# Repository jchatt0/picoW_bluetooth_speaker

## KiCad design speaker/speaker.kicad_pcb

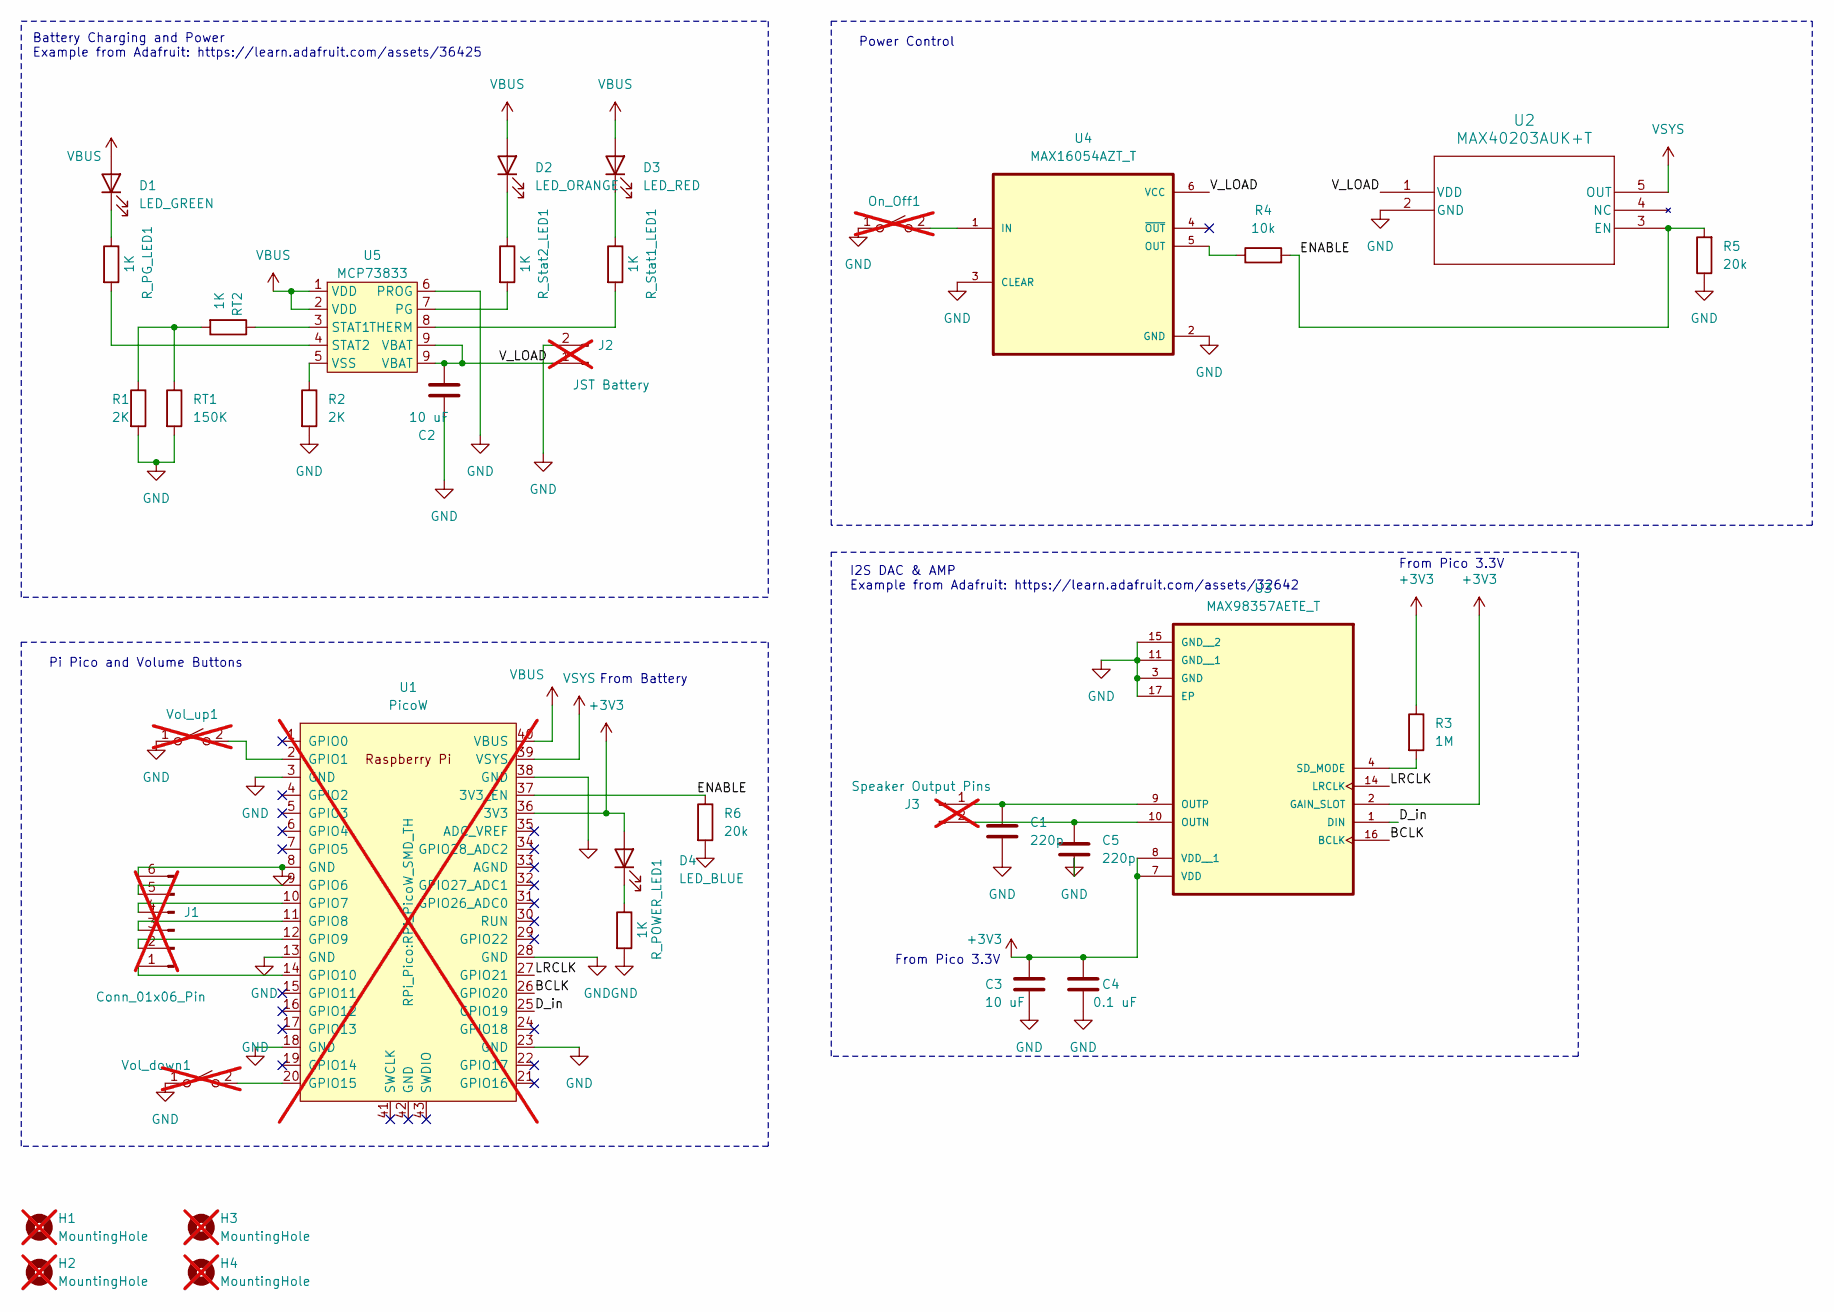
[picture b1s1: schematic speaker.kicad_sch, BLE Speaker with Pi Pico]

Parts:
C1, C5: 220p; C_0402_1005Metric_Pad0.74x0.62mm_HandSolder; MPN 0603B221K500CT
C2, C3: 10 uF; C_0603_1608Metric; MPN CL10A106MQ8NNNC
C4: 0.1 uF; C_0603_1608Metric; MPN CC0603KRX7R7BB104
D1: LED_GREEN; LED_0402_1005Metric_Pad0.77x0.64mm_HandSolder; MPN 150040GS73240
D2: LED_ORANGE; LED_0402_1005Metric_Pad0.77x0.64mm_HandSolder; MPN SML-LX0402SOC-TR
D3: LED_RED; LED_0402_1005Metric_Pad0.77x0.64mm_HandSolder; MPN XZMDK68W-2
D4: LED_BLUE; LED_0402_1005Metric_Pad0.77x0.64mm_HandSolder; MPN XZMDK68W-2
H1, H2, H3, H4: MountingHole; MountingHole_2mm; not fitted
J1: Conn_01x06_Pin; PinHeader_1x06_P1.00mm_Horizontal; not fitted
J2: JST Battery; JST_PH_S2B-PH-SM4-TB_1x02-1MP_P2.00mm_Horizontal; not fitted
J3: Speaker Output Pins; TerminalBlock_TE_282834-2_1x02_P2.54mm_Horizontal; not fitted
On_Off1: SW_SPST; SW_PUSH_6mm_H9.5mm; not fitted
R1, R2: 2K; R_0603_1608Metric; MPN ERJ-3EKF2001V
R3: 1M; R_0603_1608Metric_Pad0.98x0.95mm_HandSolder; MPN ERJ-3EKF1004V
R4: 10k; R_0603_1608Metric_Pad0.98x0.95mm_HandSolder; MPN RC0603FR-0710KL
R5, R6: 20k; R_0603_1608Metric_Pad0.98x0.95mm_HandSolder; MPN ERJ-3EKF2002V
RT1: 150K; R_0603_1608Metric; MPN RC0603FR-07150KL
RT2: 1K; R_0603_1608Metric; MPN RC0603FR-071KL
R_PG_LED1: 1K; R_0603_1608Metric; MPN RC0603FR-071KL
R_POWER_LED1: 1K; R_0603_1608Metric; MPN RC0603FR-071KL
R_Stat1_LED1, R_Stat2_LED1: 1K; R_0603_1608Metric; MPN RC0603FR-071KL
U1: PicoW; RPi_PicoW_SMD_TH; not fitted
U2: MAX40203AUK+T; 21-0057F_MXM; MPN MAX40203AUK+T
U3: MAX98357AETE_T; QFN50P300X300X80-17N; MPN MAX98357AETE_T
U4: MAX16054AZT_T; TSOT-23-6_HandSoldering; MPN MAX16054AZT_T
U5: MCP73833; MSOP10_MC_MCH-L; MPN MCP73833-CNI/UN
Vol_down1: SW_SPST; SW_PUSH_6mm_H8mm; not fitted
Vol_up1: SW_SPST; SW_PUSH_6mm_H9.5mm; not fitted

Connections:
+3V3: C3.1, C4.1, D4.2 (A), R3.1, U1.36 (3V3), U3.2 (GAIN_SLOT), U3.7 (VDD), U3.8 (VDD__1)
/BCLK: U1.26 (GPIO20), U3.16 (BCLK)
/D_in: U1.25 (GPIO19), U3.1 (DIN)
/ENABLE: R4.2, R5.2, R6.1, U1.37 (3V3_EN), U2.3 (EN)
/LRCLK: U1.27 (GPIO21), U3.14 (LRCLK)
/V_LOAD: C2.1, J2.1, U2.1 (VDD), U4.6 (VCC), U5.9 (VBAT)
GND: C1.2, C2.2, C3.2, C4.2, C5.2, J1.6, J2.2, On_Off1.1 (A), R1.2, R2.2, R5.1, R6.2, RT1.2, R_POWER_LED1.2, U1.3 (GND), U1.8 (GND), U1.13 (GND), U1.18 (GND), U1.23 (GND), U1.28 (GND), U1.38 (GND), U2.2 (GND), U3.3 (GND), U3.11 (GND__1), U3.15 (GND__2), U3.17 (EP), U4.2 (GND), U4.3 (CLEAR), U5.6 (PROG), Vol_down1.1 (A), Vol_up1.1 (A)
unnamed: D1.1 (K), R_PG_LED1.1
unnamed: D2.1 (K), R_Stat2_LED1.1
unnamed: D3.1 (K), R_Stat1_LED1.1
unnamed: D4.1 (K), R_POWER_LED1.1
unnamed: J1.1, U1.14 (GPIO10)
unnamed: J1.2, U1.12 (GPIO9)
unnamed: J1.3, U1.11 (GPIO8)
unnamed: J1.4, U1.10 (GPIO7)
unnamed: J1.5, U1.9 (GPIO6)
unnamed: C1.1, J3.1, U3.9 (OUTP)
unnamed: C5.1, J3.2, U3.10 (OUTN)
unnamed: On_Off1.2 (B), U4.1 (IN)
unnamed: R1.1, RT1.1, RT2.2
unnamed: U1.2 (GPIO1), Vol_up1.2 (B)
unnamed: U1.20 (GPIO15), Vol_down1.2 (B)
unnamed: R3.2, U3.4 (SD_MODE)
unnamed: R4.1, U4.5 (OUT)
unnamed: R_Stat2_LED1.2, U5.7 (PG)
unnamed: RT2.1, U5.3 (STAT1)
unnamed: R_PG_LED1.2, U5.4 (STAT2)
unnamed: R_Stat1_LED1.2, U5.8 (THERM)
unnamed: R2.1, U5.5 (VSS)
VBUS: D1.2 (A), D2.2 (A), D3.2 (A), U1.40 (VBUS), U5.1 (VDD), U5.2 (VDD)
VSYS: U1.39 (VSYS), U2.5 (OUT)

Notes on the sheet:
From Battery
From Pico 3.3V
Power Control
Battery Charging and Power Example from Adafruit: https://learn.adafruit.com/assets/36425
Pi Pico and Volume Buttons
I2S DAC & AMP Example from Adafruit: https://learn.adafruit.com/assets/32642

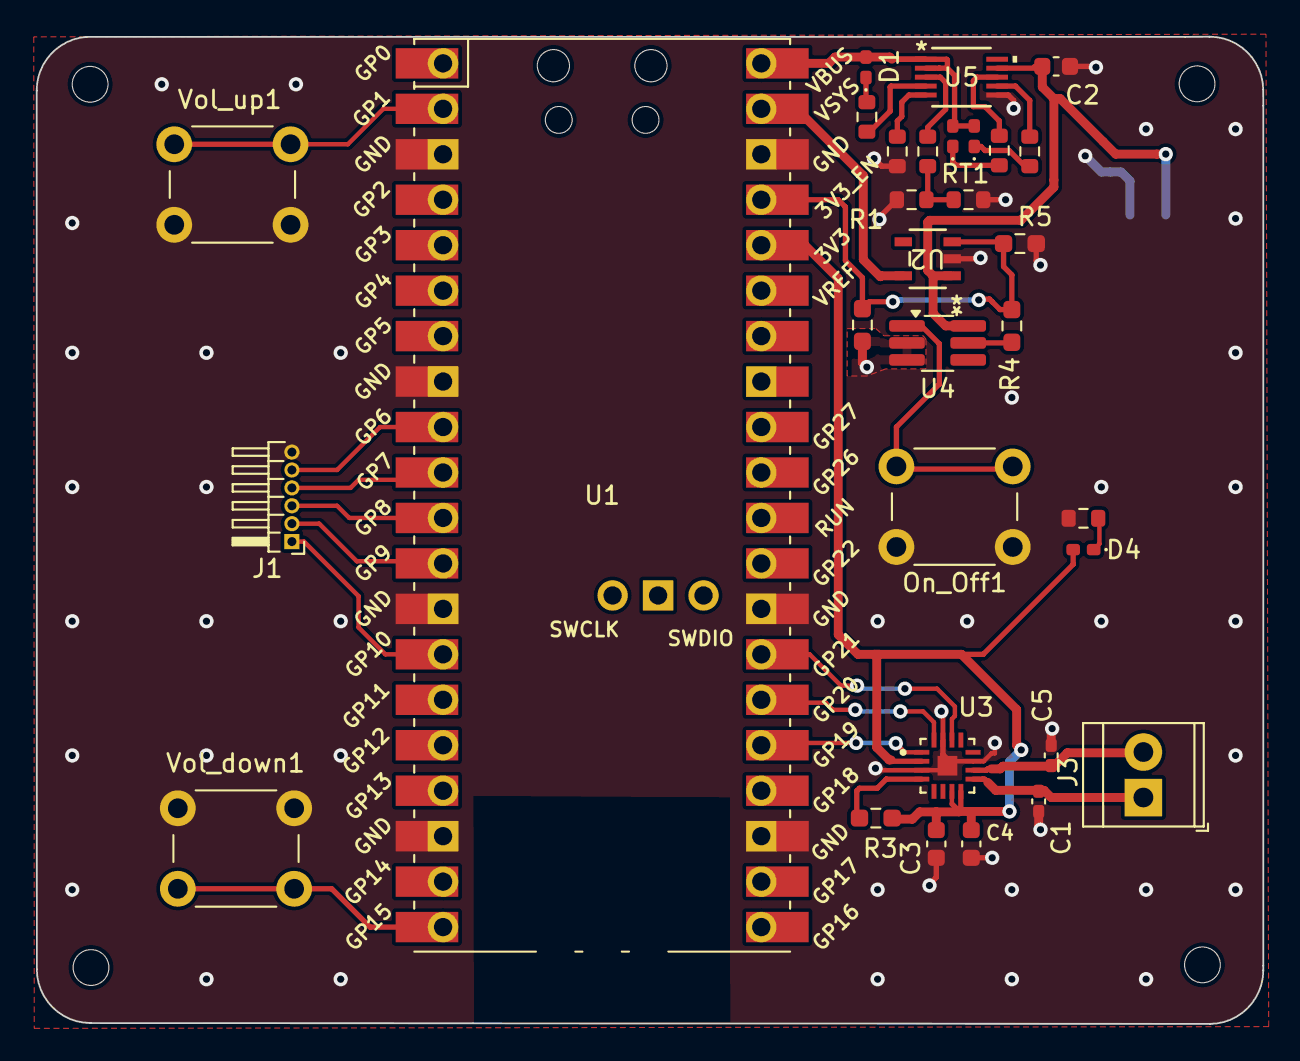
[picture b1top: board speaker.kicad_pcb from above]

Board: 2 copper layers, 68.5 x 55.2 mm, 36 parts (1 on the bottom side), 31 nets.

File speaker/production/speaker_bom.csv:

"Designator","Comment","Footprint","MPN","Qty"
"C4","0.1 uF","Capacitor_SMD:C_0603_1608Metric","CC0603KRX7R7BB104","1"
"D1","LED_GREEN","LED_SMD:LED_0402_1005Metric_Pad0.77x0.64mm_HandSolder","150040GS73240","1"
"D2","LED_ORANGE","LED_SMD:LED_0402_1005Metric_Pad0.77x0.64mm_HandSolder","SML-LX0402SOC-TR","1"
"D3","LED_RED","LED_SMD:LED_0402_1005Metric_Pad0.77x0.64mm_HandSolder","XZMDK68W-2","1"
"R3","1M","Resistor_SMD:R_0603_1608Metric_Pad0.98x0.95mm_HandSolder","ERJ-3EKF1004V","1"
"R4","10k","Resistor_SMD:R_0603_1608Metric_Pad0.98x0.95mm_HandSolder","RC0603FR-0710KL","1"
"RT1","150K","Resistor_SMD:R_0603_1608Metric","RC0603FR-07150KL","1"
"U2","MAX40203AUK+T","21-0057F_MXM","MAX40203AUK+T","1"
"U3","MAX98357AETE_T","jacob_lib:QFN50P300X300X80-17N","MAX98357AETE_T","1"
"U4","MAX16054AZT_T","Package_TO_SOT_SMD:TSOT-23-6_HandSoldering","MAX16054AZT_T","1"
"U5","MCP73833","footprints:MSOP10_MC_MCH-L","MCP73833-CNI/UN","1"
"C1,C5","220p","Capacitor_SMD:C_0402_1005Metric_Pad0.74x0.62mm_HandSolder","0603B221K500CT","2"
"C2,C3","10 uF","Capacitor_SMD:C_0603_1608Metric","CL10A106MQ8NNNC","2"
"R1,R2","2K","Resistor_SMD:R_0603_1608Metric","ERJ-3EKF2001V","2"
"R5,R6","20k","Resistor_SMD:R_0603_1608Metric_Pad0.98x0.95mm_HandSolder","ERJ-3EKF2002V","2"
"RT2,R_PG_LED1,R_Stat1_LED1,R_Stat2_LED1","1K","Resistor_SMD:R_0603_1608Metric","RC0603FR-071KL","4"

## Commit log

2024-11-13 add initial board files
2024-11-13 add fw folder, update gitignore
2024-11-13 update gitignore
2024-11-14 add header
2024-11-14 update bom
2024-11-14 updated bom and cpl
2024-11-14 update schematic
2024-11-17 add power led
2024-11-20 changed footprint for battery connector
